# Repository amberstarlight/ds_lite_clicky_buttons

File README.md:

# NDSL Clicky Buttons

Forked from [`facelesstech/ds_lite_clicky_buttons`][0], his original blog post can be found [here][1].

### Motherboard reference

| Test Point | Function             |
|------------|----------------------|
| P00        | A                    |
| P01        | B                    |
| P02        | SELECT               |
| P03        | START                |
| P04        | RIGHT                |
| P05        | LEFT                 |
| P06        | UP                   |
| P07        | DOWN                 |
| P08        | L_TRIGGER            |
| P09        | R_TRIGGER            |
| R00        | X                    |
| R01        | Y                    |
| LEDC2      | GND                  |
| SPL0       | L_SPEAKER+           |
| LEDA2      | Top screen backlight |

To bypass the top screen, a 330-Ohm resistor should be bridged to LEDA2 and LEDC2.

[0]: https://github.com/facelesstech/ds_lite_clicky_buttons
[1]: https://facelesstech.wordpress.com/2022/07/23/ds-lite-clicky-buttons/

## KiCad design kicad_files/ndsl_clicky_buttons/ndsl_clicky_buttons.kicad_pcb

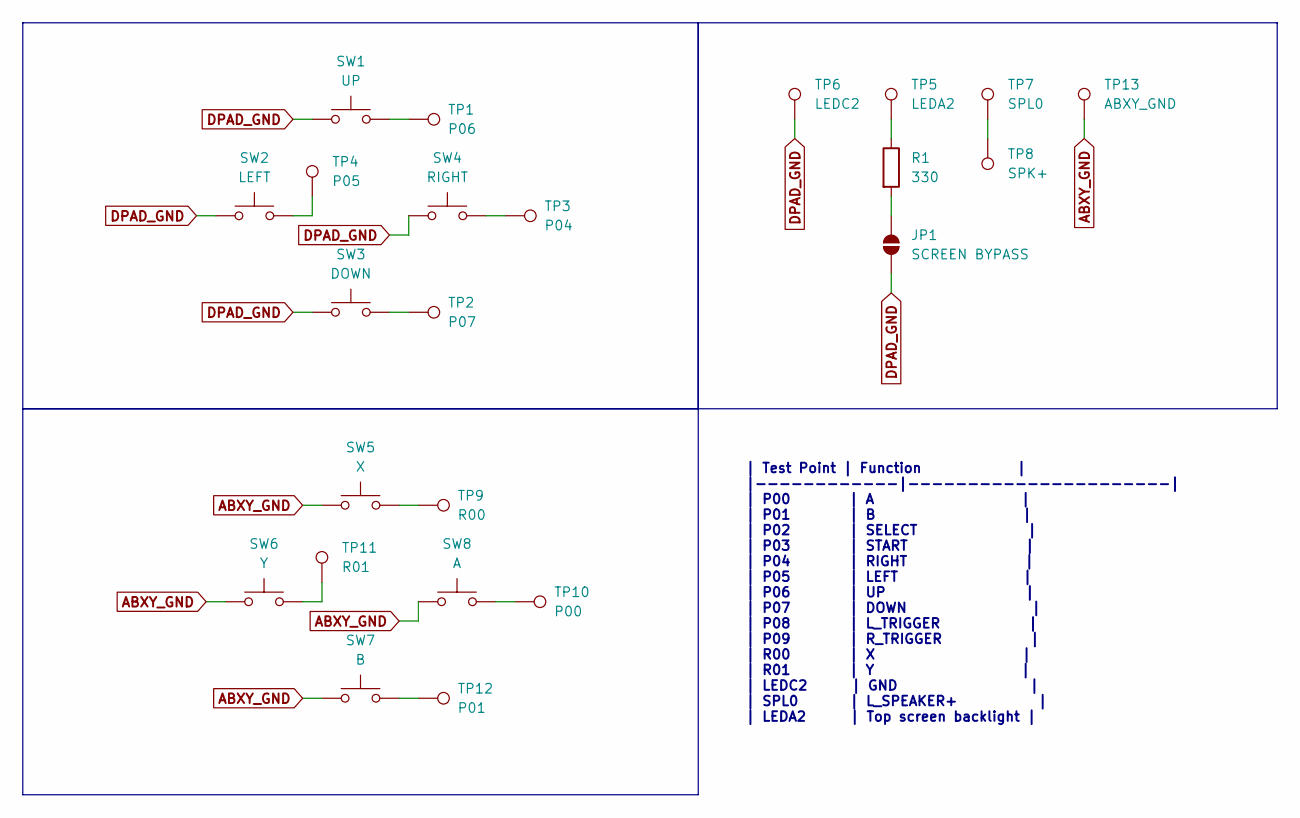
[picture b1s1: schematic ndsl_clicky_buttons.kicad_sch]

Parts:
JP1: SCREEN BYPASS; SolderJumper-2_P1.3mm_Open_RoundedPad1.0x1.5mm
R1: 330; R_0603_1608Metric_Pad0.98x0.95mm_HandSolder
SW1: UP; ALPS_SKRR
SW2: LEFT; ALPS_SKRR
SW3: DOWN; ALPS_SKRR
SW4: RIGHT; ALPS_SKRR
SW5: X; ALPS_SKRR
SW6: Y; ALPS_SKRR
SW7: B; ALPS_SKRR
SW8: A; ALPS_SKRR
TP1: P06; TestPoint_THTPad_D1.5mm_Drill1.0mm
TP2: P07; TestPoint_THTPad_D1.5mm_Drill1.0mm
TP3: P04; TestPoint_THTPad_D1.5mm_Drill1.0mm
TP4: P05; TestPoint_THTPad_D1.5mm_Drill1.0mm
TP5: LEDA2; TestPoint_THTPad_D1.5mm_Drill1.0mm
TP6: LEDC2; TestPoint_THTPad_D1.5mm_Drill1.0mm
TP7: SPL0; TestPoint_THTPad_D1.5mm_Drill1.0mm
TP8: SPK+; TestPoint_Pad_2.0x2.0mm
TP9: R00; TestPoint_THTPad_D1.5mm_Drill1.0mm
TP10: P00; TestPoint_THTPad_D1.5mm_Drill1.0mm
TP11: R01; TestPoint_THTPad_D1.5mm_Drill1.0mm
TP12: P01; TestPoint_THTPad_D1.5mm_Drill1.0mm
TP13: ABXY_GND; TestPoint_Pad_2.0x2.0mm

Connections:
ABXY_GND: SW5.1, SW6.1, SW7.1, SW8.1, TP13.1
DPAD_GND: JP1.1 (A), SW1.1, SW2.1, SW3.1, SW4.1, TP6.1
unnamed: JP1.2 (B), R1.2
unnamed: R1.1, TP5.1
unnamed: SW1.2, TP1.1
unnamed: SW2.2, TP4.1
unnamed: SW3.2, TP2.1
unnamed: SW4.2, TP3.1
unnamed: SW5.2, TP9.1
unnamed: SW6.2, TP11.1
unnamed: SW7.2, TP12.1
unnamed: SW8.2, TP10.1
unnamed: TP7.1, TP8.1

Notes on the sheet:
| Test Point | Function | |------------|----------------------| | P00 | A | | P01 | B | | P02 | SELECT | | P03 | START | | P04 | RIGHT | | P05 | LEFT | | P06 | UP | | P07 | DOWN | | P08 | L_TRIGGER | | P09 | R_TRIGGER | | R00 | X | | R01 | Y | | LEDC2 | GND | | SPL0 | L_SPEAKER+ | | LEDA2 | Top scr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

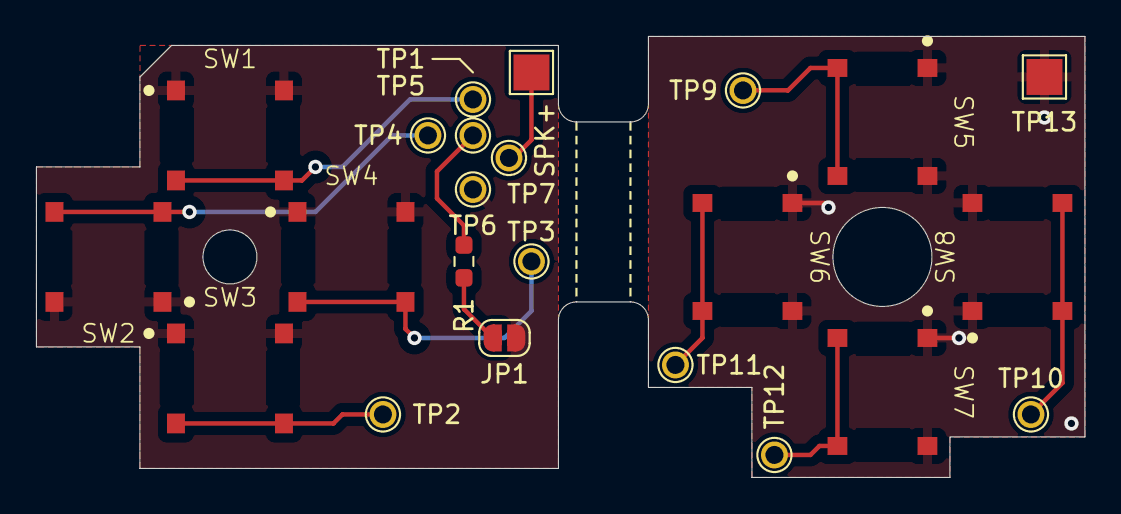
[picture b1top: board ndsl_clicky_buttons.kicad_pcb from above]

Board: 2 copper layers, 58.2 x 24.5 mm, 23 parts (0 on the bottom side), 13 nets.

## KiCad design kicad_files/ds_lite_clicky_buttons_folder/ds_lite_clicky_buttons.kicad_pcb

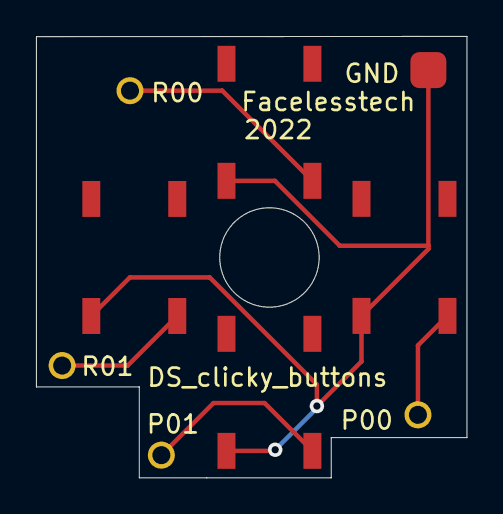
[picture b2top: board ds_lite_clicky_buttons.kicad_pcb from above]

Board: 2 copper layers, 23.9 x 24.5 mm, 9 parts (0 on the bottom side), 5 nets.

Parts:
GND: TestPoint; 2mm_test_point_smd
P00, P01: TestPoint; 1mm_test_point
R00, R01: TestPoint; 1mm_test_point
SW1, SW2, SW3, SW4: SW_Push; gba_sp_buttons

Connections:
unnamed: GND.1, SW1.1, SW2.1, SW3.1, SW4.1
unnamed: R00.1, SW1.2
unnamed: R01.1, SW2.2
unnamed: P01.1, SW3.2
unnamed: P00.1, SW4.2

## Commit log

2025-06-20 Refactor part 1: D-PAD
2025-06-20 Add custom test point footprint
2025-06-21 Add ALPS SKRR footprint
2025-06-26 Add solder jumper to enable Macro screen bypass
2025-07-04 Update d-pad PCB
2025-07-04 Put both boards together
